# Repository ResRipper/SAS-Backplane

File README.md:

# SAS Backplane

> [!WARNING]
> Not final version, DO NOT USE

## Spec

- SFF-8087 -> 4x SAS 3.5 inch drive
- Power: 120 W

    | PWR Lane | Source   | Current per drive (A) | Total capacity (W) |
    | -------- | -------- | --------------------- | ------------------ |
    | 12V      | PSU      | 2                     | 96                 |
    | 5V       | 12V Lane | 1.2                   | 24                 |

## Change log

- v1.0 -> v1.1
    - SCH: v1.5
        - Use 2x `TPS82130` for 12V -> 5V conversion
            - Lower BOM count / cost
            - Smaller physical size
        - +12V power input connector
          - 4x M4 screws (2x +12, 2x GND) -> 1x ATX 4 pin connector
        - +12V filter group
          - 47uF cap -> 22uF ceramic cap
        - Add two 47uF caps to +12V input
        - Remove header for drive stat, remove `DNP` attribute for activity LEDs

    - PCB: v1.2
        - Change drive layout to vertical
        - Increase slot height from `27mm` to `28mm` for more airflow
        - Shrink board size to `100 x 90 mm`

## References

- https://pactech-inc.com/wp-content/uploads/2014/06/AMPH-8782-XXX-Send-out_01.jpg
- https://www.seagate.com/content/dam/seagate/assets/support/internal-hard-drive/enterprise-hard-drives/exos-x24/_shared/files/Seagate_Exos_24_SAS_ISE-SED-FIPs(12-16-20-24TB)_Rev-A.pdf
- https://www.seagate.com/content/dam/seagate/migrated-assets/www-content/product-content/enterprise-hdd-fam/exos-7e10/_shared/docs/100870879e.pdf
- https://www.seagate.com/content/dam/seagate/migrated-assets/www-content/manuals/exos-x-2x18/pdf/203859600a.pdf
- https://sata-io.org/system/files/specifications/SerialATA_Revision_3_1_Gold.pdf
- SFF-8609

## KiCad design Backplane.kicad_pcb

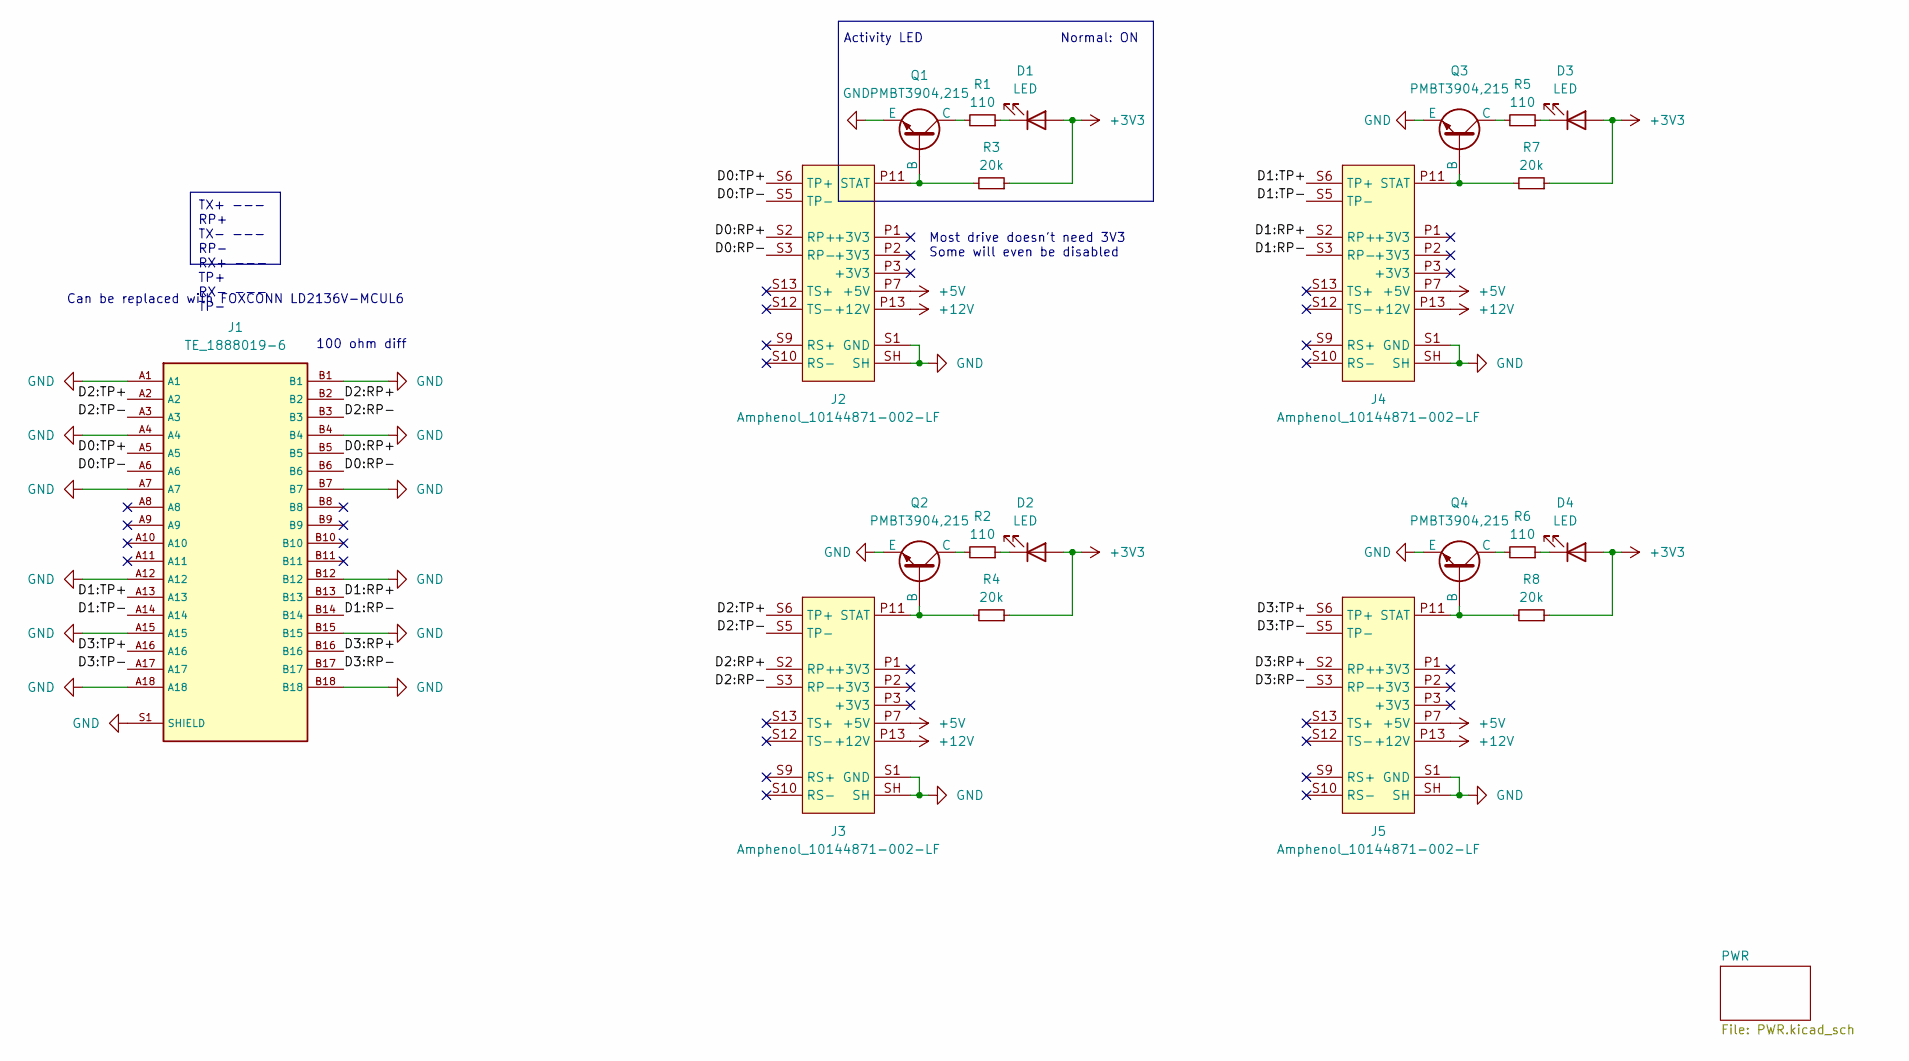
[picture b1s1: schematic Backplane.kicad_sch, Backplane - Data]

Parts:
D1, D2, D3, D4: LED; LED_0603_1608Metric; LCSC C7496818
J1: TE_1888019-6
J2, J3, J4, J5: Amphenol_10144871-002-LF; Amphenol_10144871-002-TRLF
Q1, Q2, Q3, Q4: PMBT3904,215; SOT-23; LCSC C8667
R1, R2, R5, R6: 110; R_0402_1005Metric; LCSC C295884
R3, R4, R7, R8: 20k; R_0402_1005Metric; LCSC C137902

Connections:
+3V3: D1.2 (A), D2.2 (A), D3.2 (A), D4.2 (A), R3.1, R4.1, R7.1, R8.1; also elsewhere on the board
+5V: J2.P7 (+5V), J2.P8 (+5V), J2.P9 (+5V), J3.P7 (+5V), J3.P8 (+5V), J3.P9 (+5V), J4.P7 (+5V), J4.P8 (+5V), J4.P9 (+5V), J5.P7 (+5V), J5.P8 (+5V), J5.P9 (+5V); also elsewhere on the board
+12V: J2.P13 (+12V), J2.P14 (+12V), J2.P15 (+12V), J3.P13 (+12V), J3.P14 (+12V), J3.P15 (+12V), J4.P13 (+12V), J4.P14 (+12V), J4.P15 (+12V), J5.P13 (+12V), J5.P14 (+12V), J5.P15 (+12V); also elsewhere on the board
/D0:RP+: J1.B5, J2.S2 (RP+)
/D0:RP-: J1.B6, J2.S3 (RP-)
/D0:TP+: J1.A5, J2.S6 (TP+)
/D0:TP-: J1.A6, J2.S5 (TP-)
/D1:RP+: J1.B13, J4.S2 (RP+)
/D1:RP-: J1.B14, J4.S3 (RP-)
/D1:TP+: J1.A13, J4.S6 (TP+)
/D1:TP-: J1.A14, J4.S5 (TP-)
/D2:RP+: J1.B2, J3.S2 (RP+)
/D2:RP-: J1.B3, J3.S3 (RP-)
/D2:TP+: J1.A2, J3.S6 (TP+)
/D2:TP-: J1.A3, J3.S5 (TP-)
/D3:RP+: J1.B16, J5.S2 (RP+)
/D3:RP-: J1.B17, J5.S3 (RP-)
/D3:TP+: J1.A16, J5.S6 (TP+)
/D3:TP-: J1.A17, J5.S5 (TP-)
GND: J1.A1, J1.A4, J1.A7, J1.A12, J1.A15, J1.A18, J1.B1, J1.B4, J1.B7, J1.B12, J1.B15, J1.B18, J1.S1 (SHIELD), J1.S2 (SHIELD), J1.S3 (SHIELD), J1.S4 (SHIELD), J1.S5 (SHIELD), J1.S6 (SHIELD), J2.P4 (GND), J2.P5 (GND), J2.P6 (GND), J2.P10 (GND), J2.P12 (GND), J2.S1 (GND), J2.S4 (GND), J2.S7 (GND), J2.S8 (GND), J2.S11 (GND), J2.S14 (GND), J2.SH, J3.P4 (GND), J3.P5 (GND), J3.P6 (GND), J3.P10 (GND), J3.P12 (GND), J3.S1 (GND), J3.S4 (GND), J3.S7 (GND), J3.S8 (GND), J3.S11 (GND), J3.S14 (GND), J3.SH, J4.P4 (GND), J4.P5 (GND), J4.P6 (GND), J4.P10 (GND), J4.P12 (GND), J4.S1 (GND), J4.S4 (GND), J4.S7 (GND), J4.S8 (GND), J4.S11 (GND), J4.S14 (GND), J4.SH, J5.P4 (GND), J5.P5 (GND), J5.P6 (GND), J5.P10 (GND), J5.P12 (GND), J5.S1 (GND), J5.S4 (GND), J5.S7 (GND), J5.S8 (GND), J5.S11 (GND), J5.S14 (GND), J5.SH, Q1.3 (E), Q2.3 (E), Q3.3 (E), Q4.3 (E); also elsewhere on the board
unnamed: D1.1 (K), R1.1
unnamed: D2.1 (K), R2.1
unnamed: D3.1 (K), R5.1
unnamed: D4.1 (K), R6.1
unnamed: J2.P11 (STAT), Q1.2 (B), R3.2
unnamed: J3.P11 (STAT), Q2.2 (B), R4.2
unnamed: J4.P11 (STAT), Q3.2 (B), R7.2
unnamed: J5.P11 (STAT), Q4.2 (B), R8.2
unnamed: Q1.1 (C), R1.2
unnamed: Q2.1 (C), R2.2
unnamed: Q3.1 (C), R5.2
unnamed: Q4.1 (C), R6.2

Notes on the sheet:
TX+ --- RP+ TX- --- RP- RX+ --- TP+ RX- --- TP-
100 ohm diff
Most drive doesn't need 3V3 Some will even be disabled
Normal: ON
Can be replaced with FOXCONN LD2136V-MCUL6
Activity LED

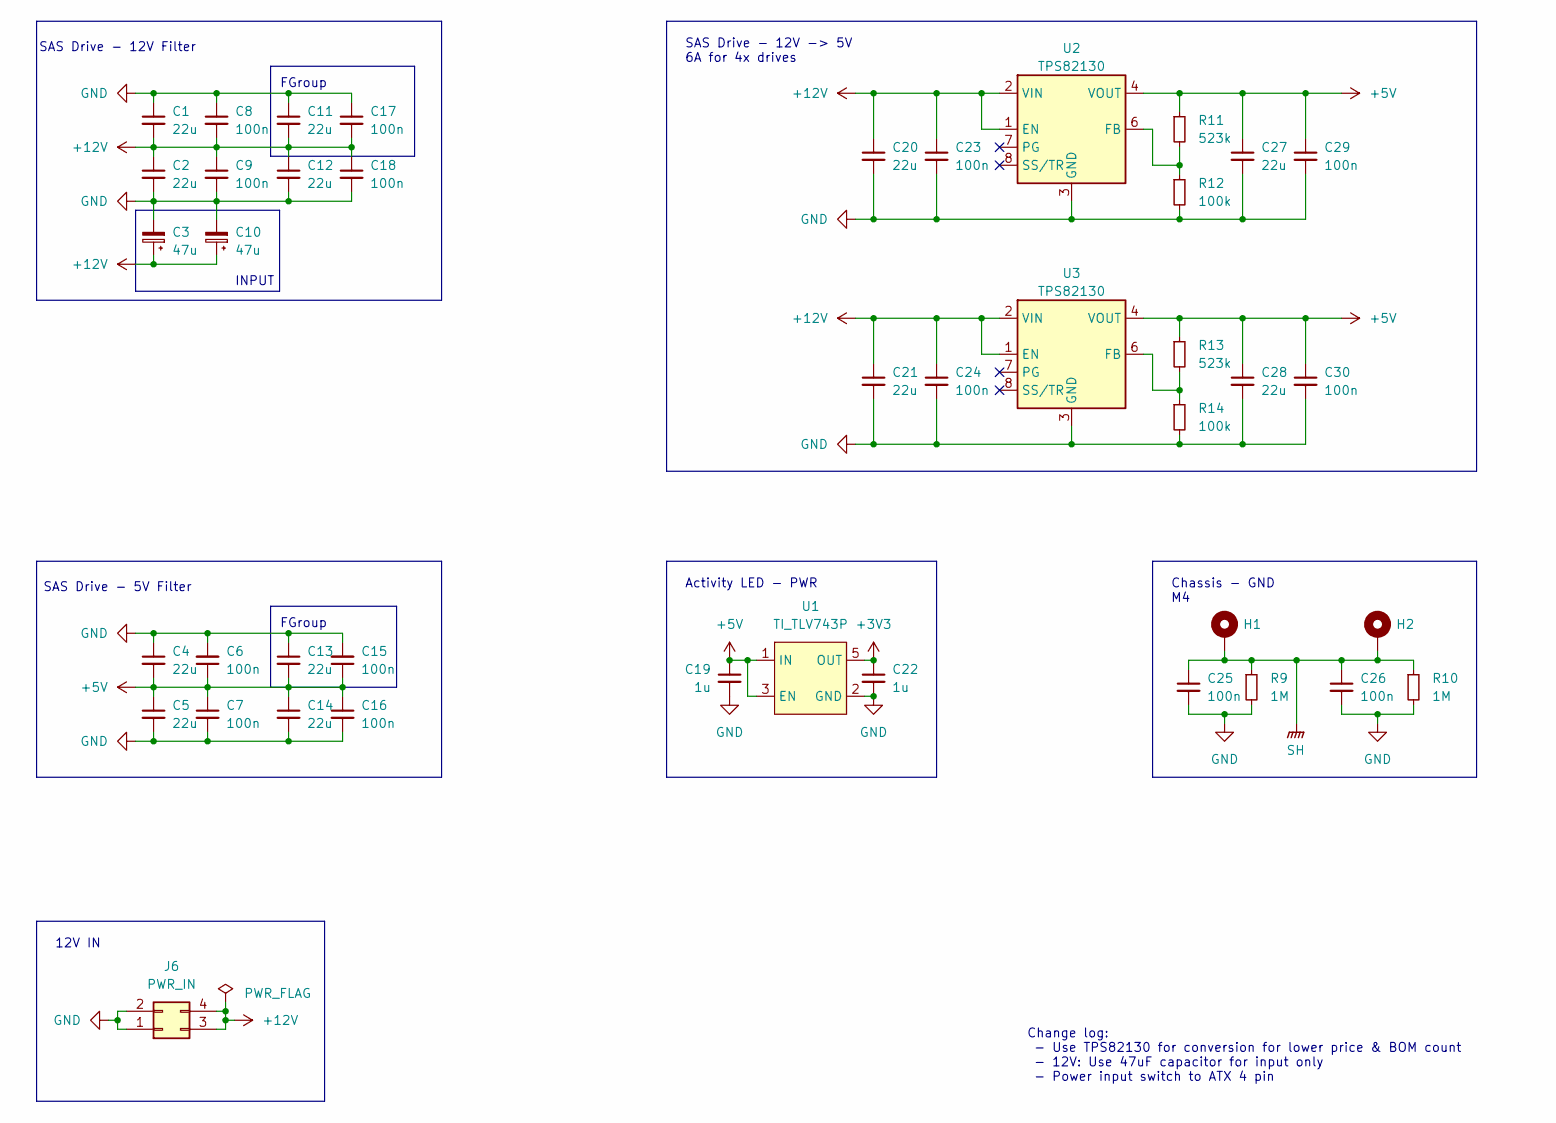
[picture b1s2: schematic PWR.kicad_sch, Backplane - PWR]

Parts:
C1, C2, C11, C12, C20, C21: 22u; C_0805_2012Metric; LCSC C602037
C3, C10: 47u; CP_Elec_6.3x5.8; LCSC C2157870
C4, C5, C13, C14, C27, C28: 22u; C_0603_1608Metric; LCSC C159801
C6, C7, C15, C16, C29, C30: 100n; C_0402_1005Metric; LCSC C60474
C8, C9, C17, C18, C23, C24: 100n; C_0402_1005Metric; LCSC C105883
C19, C22: 1u; C_0402_1005Metric; LCSC C52923
C25, C26: 100n; C_1206_3216Metric; LCSC C23631
H1, H2: MountingHole_4.3mm_M4_Pad_TopBottom
J6: PWR_IN; XKB_X9357WR-2x02-N2SN; LCSC C388758
R9, R10: 1M; R_0603_1608Metric; LCSC C144621
R11, R13: 523k; R_0402_1005Metric; LCSC C227128
R12, R14: 100k; R_0402_1005Metric; LCSC C60491
U1: TI_TLV743P; Ti_DBV0005A; LCSC C408972
U2, U3: TPS82130; Texas_SIL0008D_MicroSiP-8-1EP_2.8x3mm_P0.65mm_EP1.1x1.9mm_T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; LCSC C473914

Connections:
+3V3: C22.1, U1.5 (OUT); also elsewhere on the board
+5V: C4.2, C5.1, C6.1, C7.1, C13.2, C14.1, C15.1, C16.1, C19.1, C27.1, C28.1, C29.1, C30.1, R11.1, R13.1, U1.1 (IN), U1.3 (EN), U2.4 (VOUT), U2.5 (VOUT), U3.4 (VOUT), U3.5 (VOUT); also elsewhere on the board
+12V: C1.2, C2.1, C3.1, C8.2, C9.1, C10.1, C11.2, C12.1, C17.2, C18.1, C20.1, C21.1, C23.1, C24.1, J6.3, J6.4, U2.1 (EN), U2.2 (VIN), U3.1 (EN), U3.2 (VIN); also elsewhere on the board
GND: C1.1, C2.2, C3.2, C4.1, C5.2, C6.2, C7.2, C8.1, C9.2, C10.2, C11.1, C12.2, C13.1, C14.2, C15.2, C16.2, C17.1, C18.2, C19.2, C20.2, C21.2, C22.2, C23.2, C24.2, C25.2, C26.2, C27.2, C28.2, C29.2, C30.2, J6.1, J6.2, R9.2, R10.2, R12.2, R14.2, U1.2 (GND), U2.3 (GND), U2.9 (GND), U3.3 (GND), U3.9 (GND); also elsewhere on the board
unnamed: R11.2, R12.1, U2.6 (FB)
unnamed: R13.2, R14.1, U3.6 (FB)
SH: C25.1, C26.1, H1.1, H2.1, R9.1, R10.1

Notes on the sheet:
Change log: - Use TPS82130 for conversion for lower price & BOM count - 12V: Use 47uF capacitor for input only - Power input switch to ATX 4 pin
SAS Drive - 12V -> 5V 6A for 4x drives
12V IN
Chassis - GND M4
INPUT
FGroup
Activity LED - PWR
SAS Drive - 12V Filter
SAS Drive - 5V Filter

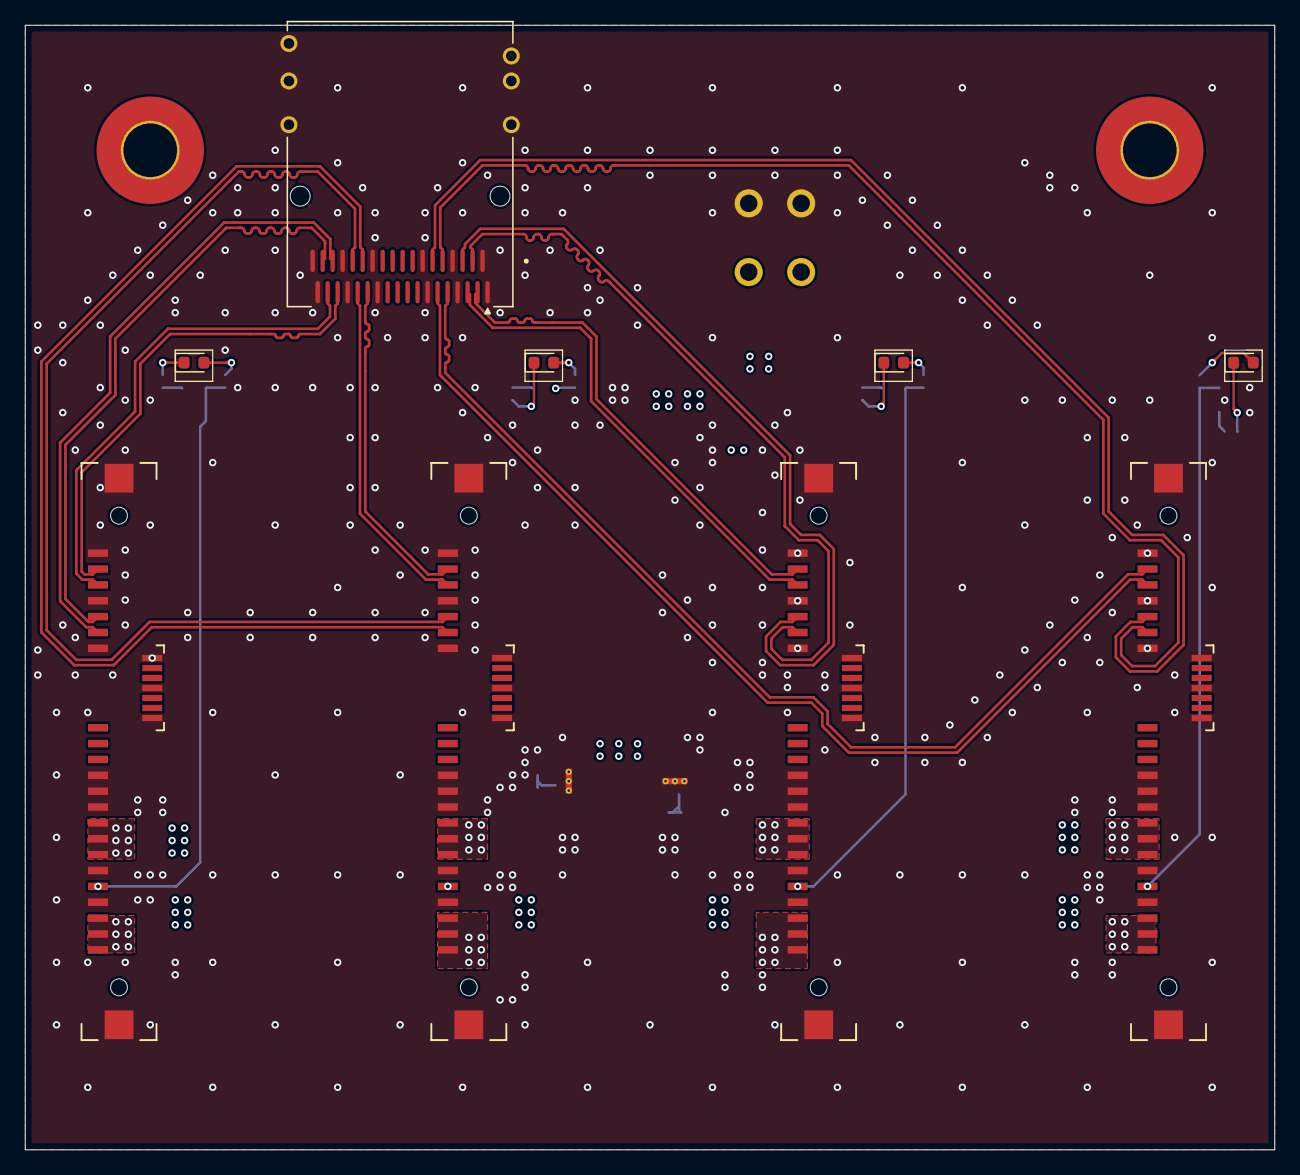
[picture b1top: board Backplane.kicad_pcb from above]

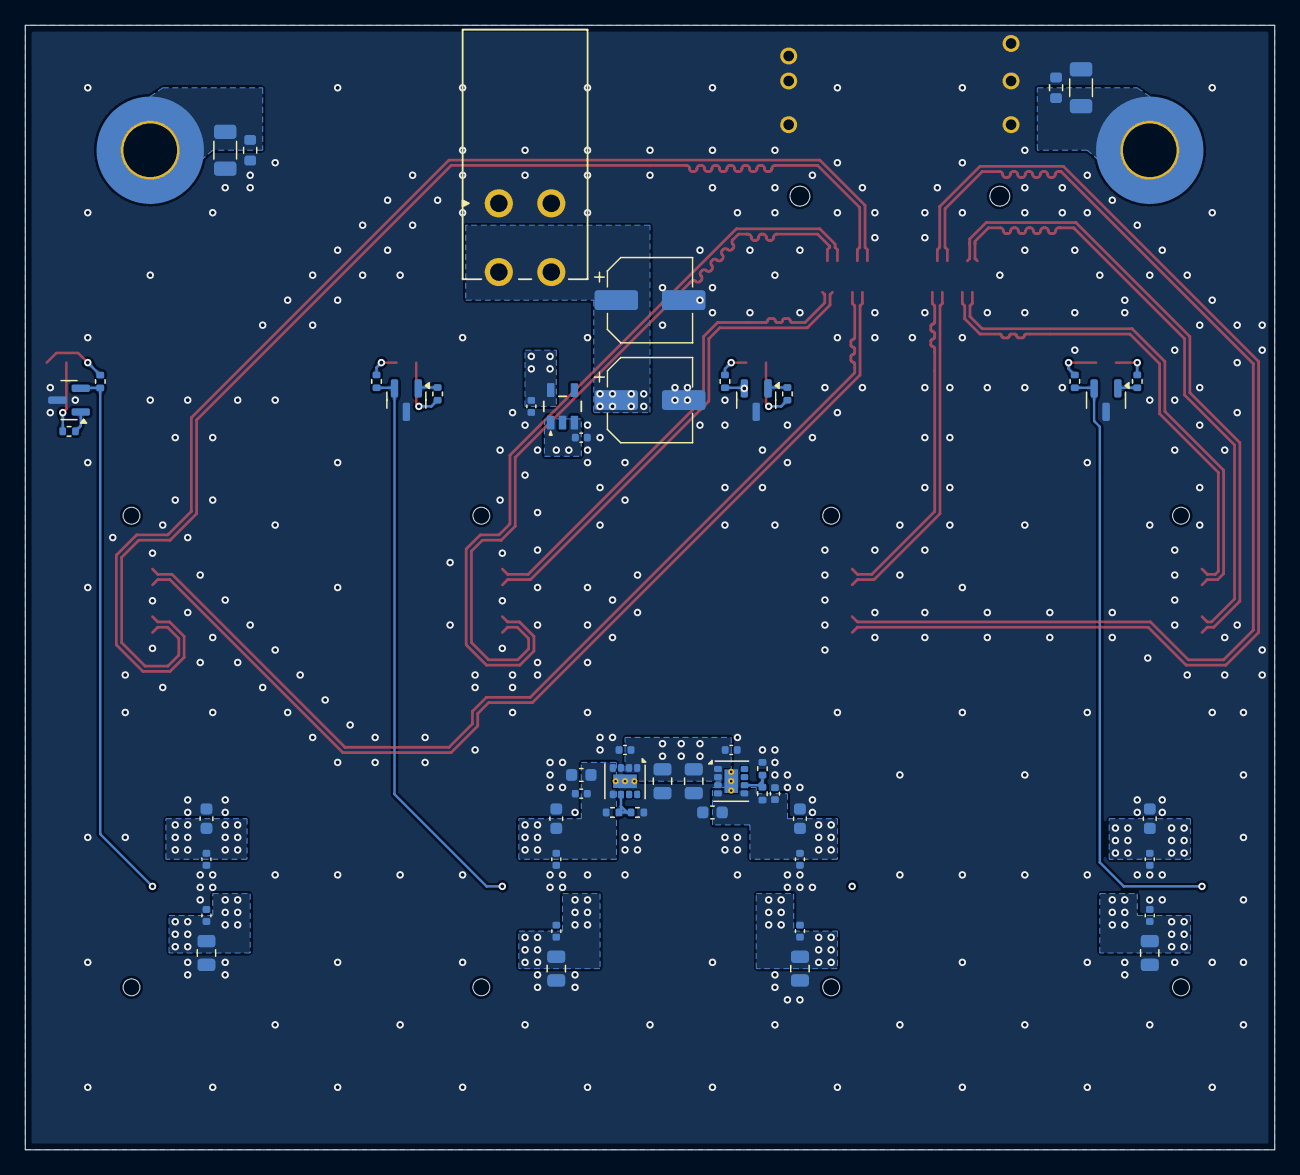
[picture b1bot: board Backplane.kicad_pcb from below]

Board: 4 copper layers, 100.0 x 90.0 mm, 63 parts (52 on the bottom side), 35 nets.

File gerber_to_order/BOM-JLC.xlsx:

Designator | Comment | Datasheet | Footprint | Qty | LCSC | PN | Vendor
C1,C2,C11,C12,C20,C21 | 22u | ~ | Capacitor_SMD:C_0805_2012Metric | 6 | C602037 | CL21A226MAYNNNE | Samsung
C3,C10 | 47u | https://www.chemi-con.co.jp/en/products/detail-condenser.php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 | Capacitor_SMD:CP_Elec_6.3x5.8 | 2 | C2157870 | HHXE350ARA470MF61G | NCC
C4,C5,C13,C14,C27,C28 | 22u | ~ | Capacitor_SMD:C_0603_1608Metric | 6 | C159801 | CL10A226MQ8NRNE | Samsung
C6,C7,C15,C16,C29,C30 | 100n | ~ | Capacitor_SMD:C_0402_1005Metric | 6 | C60474 | CC0402KRX7R7BB104 | YAGEO
C8,C9,C17,C18,C23,C24 | 100n | ~ | Capacitor_SMD:C_0402_1005Metric | 6 | C105883 | CC0402KRX7R8BB104 | YAGEO
C19,C22 | 1u | ~ | Capacitor_SMD:C_0402_1005Metric | 2 | C52923 | CL05A105KA5NQNC | Samsung
C25,C26 | 100n | ~ | Capacitor_SMD:C_1206_3216Metric | 2 | C23631 | CC1206KKX7RDBB102 | YAGEO
D1,D2,D3,D4 | LED | ~ | LED_SMD:LED_0603_1608Metric | 4 | C7496818 | P2-0603G1TS2-06T-002 | TUOZHAN
J1 | TE_1888019-6 | https://www.te.com/commerce/DocumentDelivery/DDEController?A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 | Library:TE_1888019-6 | 1 | C2979967 | LD2136V-MCUL6 | FOXCONN
J2,J3,J4,J5 | Amphenol_10144871-002-LF | https://cdn.amphenol-cs.com/media/wysiwyg/files/drawing/1014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 | Library:Amphenol_10144871-002-TRLF | 4 | C2906136 | 91904-291512 | Umaxconn
J6 | PWR_IN | https://www.helloxkb.com/public/images/pdf/X9357WR-2xXX-N2SN.pdf | Library:XKB_X9357WR-2x02-N2SN | 1 | C388758 | X9357WR-2x02-N2SN | XKB Connecitity
Q1,Q2,Q3,Q4 | PMBT3904,215 | https://assets.nexperia.com/documents/data-sheet/PMBT3904.pdf | Package_TO_SOT_SMD:SOT-23 | 4 | C8667 | PMBT3904,215 | Nexperia
R1,R2,R5,R6 | 110 | ~ | Resistor_SMD:R_0402_1005Metric | 4 | C295884 | RC0402JR-07110RL | YAGEO
R3,R4,R7,R8 | 20k | ~ | Resistor_SMD:R_0402_1005Metric | 4 | C137902 | RC0402JR-0720KL | YAGEO
R9,R10 | 1M | ~ | Resistor_SMD:R_0603_1608Metric | 2 | C144621 | AC0603JR-071ML | YAGEO
R11,R13 | 523k | ~ | Resistor_SMD:R_0402_1005Metric | 2 | C227128 | AC0402FR-07523KL | YAGEO
R12,R14 | 100k | ~ | Resistor_SMD:R_0402_1005Metric | 2 | C60491 | RC0402FR-07100KL | YAGEO
U1 | TI_TLV743P | https://www.ti.com/lit/ds/symlink/tlv743p.pdf | Library:Ti_DBV0005A | 1 | C408972 | TLV74333PDBVR | Texas Instruments
U2,U3 | TPS82130 | http://www.ti.com/lit/ds/symlink/tps82130.pdf | Package_LGA:Texas_SIL0008D_MicroSiP-8-1EP_2.8x3mm_P0.65mm_EP1.1x1.9mm_ThermalVi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 | 2 | C473914 | TPS82130SILR | Texas Instruments

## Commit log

2024-05-27 Add .gitignore
2024-05-27 Version 1.0
2024-05-27 Create LICENSE
2024-06-08 Version 1.1
